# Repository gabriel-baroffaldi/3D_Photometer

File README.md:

3D Printable LED Photometer © 2025 by Gabriel Baroffaldi Piassalonga, Paulo Clairmont Feitosa de Lima Gomes, São Paulo State University is licensed under Creative Commons Attribution-ShareAlike 4.0 International. To view a copy of this license, visit https://creativecommons.org/licenses/by-sa/4.0/

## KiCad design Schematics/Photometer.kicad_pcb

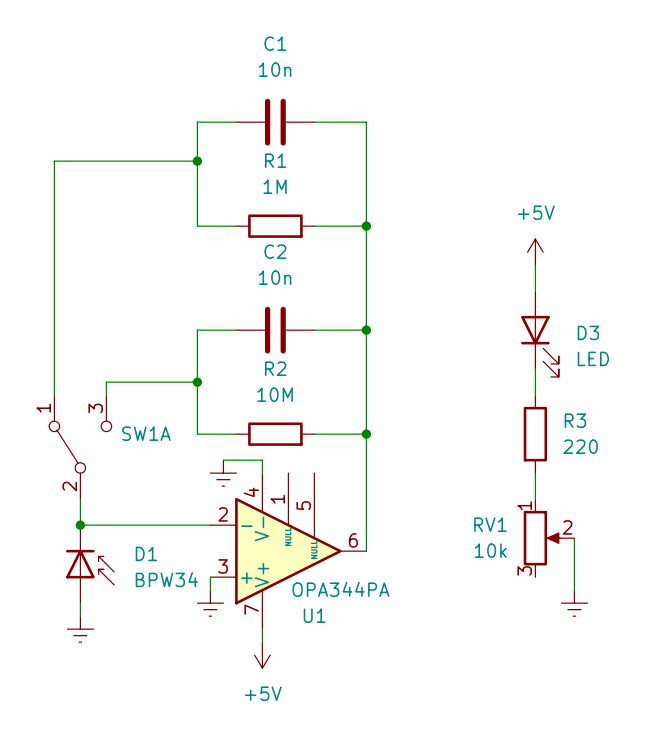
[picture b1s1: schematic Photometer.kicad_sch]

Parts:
C1, C2: 10n; C_Rect_L9.0mm_W3.6mm_P7.50mm_MKT
D1: BPW34; SolderWire-0.1sqmm_1x02_P3.6mm_D0.4mm_OD1mm
D3: LED; SolderWire-0.1sqmm_1x02_P3.6mm_D0.4mm_OD1mm
R1: 1M; R_Axial_DIN0204_L3.6mm_D1.6mm_P7.62mm_Horizontal
R2: 10M; R_Axial_DIN0204_L3.6mm_D1.6mm_P7.62mm_Horizontal
R3: 220; R_Axial_DIN0204_L3.6mm_D1.6mm_P7.62mm_Horizontal
RV1: 10k; SolderWire-0.1sqmm_1x03_P3.6mm_D0.4mm_OD1mm
SW1: SW_DPDT_x2; SolderWire-0.1sqmm_1x03_P3.6mm_D0.4mm_OD1mm
U1: OPA344PA; DIP-8_W7.62mm_Socket_LongPads

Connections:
+5V: D3.2 (A), U1.7 (V+)
Earth: D1.2 (A), RV1.2, U1.3 (+), U1.4 (V-)
unnamed: C1.2, C2.2, R1.2, R2.2, U1.6
unnamed: D1.1 (K), SW1.2 (B), U1.2 (-)
unnamed: D3.1 (K), R3.1
unnamed: R3.2, RV1.1
unnamed: C1.1, R1.1, SW1.1 (A)
unnamed: C2.1, R2.1, SW1.3 (C)

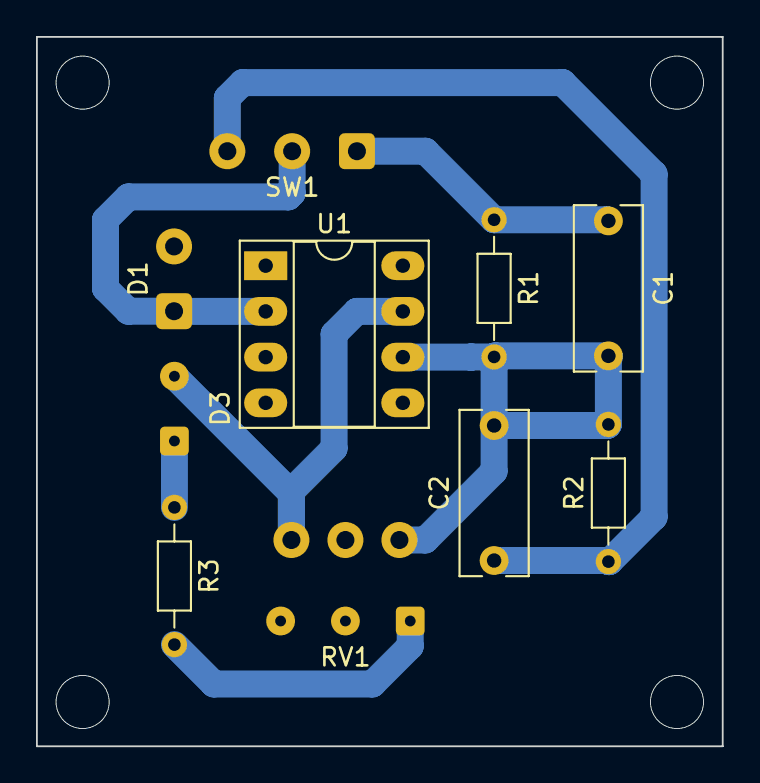
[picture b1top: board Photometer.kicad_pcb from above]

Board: 2 copper layers, 38.1 x 39.4 mm, 10 parts (0 on the bottom side), 8 nets.

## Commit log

2025-02-11 Create CAD
2025-02-11 Create teste
2025-05-28 Create License
